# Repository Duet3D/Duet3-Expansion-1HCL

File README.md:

# Duet 3 Expansion 1HCL
The Duet 3 Expansion 1HCL is a CAN-FD connected expansion board for the [Duet 3 Mainboard 6HC](https://www.duet3d.com/duet3mainboard6hc), [Duet 3 Mainboard 6XD](https://www.duet3d.com/duet3mainboard6xd) and [Duet 3 Mini 5+](https://www.duet3d.com/duet3mini5plus) that is designed to provide a high current stepper motor driver, combined with multiple interfaces for position feedback. It has a number of peripheral inputs and outputs for functions such as sensing motor temperature, controlling a brake and axis endstop.

Product page is here: https://www.duet3d.com/duet-3-expansion-1hcl

Documentation is here: https://docs.duet3d.com/Duet3D_hardware/Duet_3_family/Duet_3_Expansion_1HCL

As always please discuss this on the Duet3d forum: https://forum.duet3d.com/

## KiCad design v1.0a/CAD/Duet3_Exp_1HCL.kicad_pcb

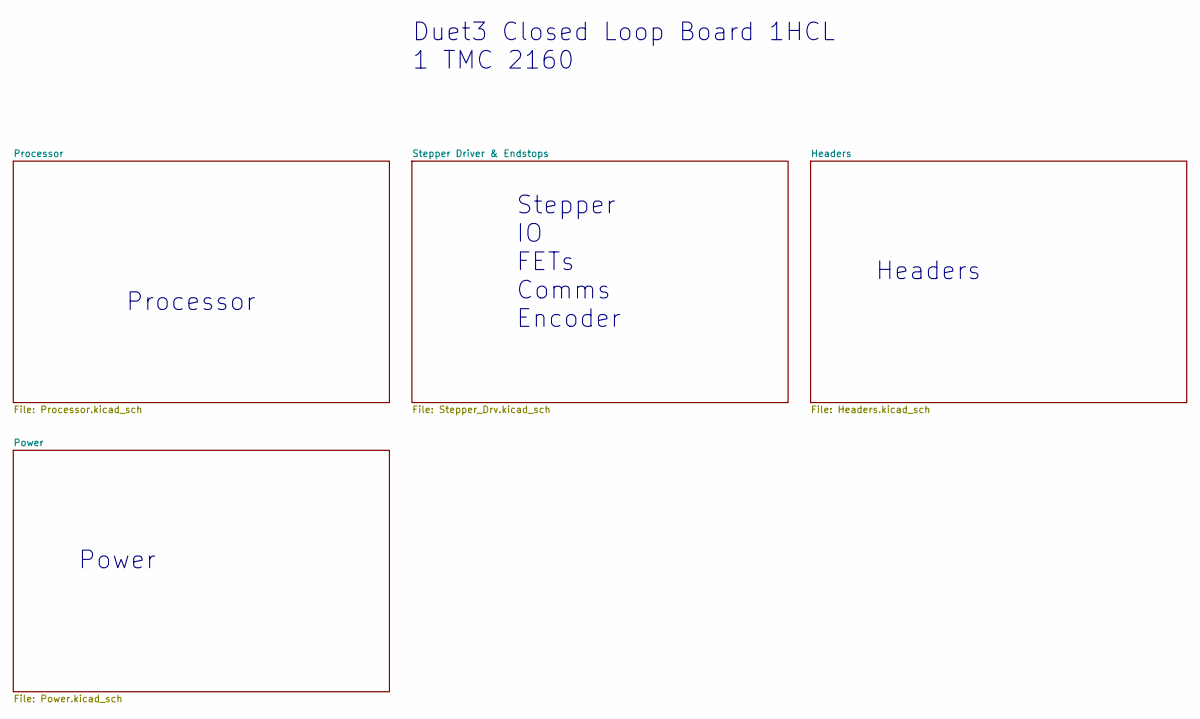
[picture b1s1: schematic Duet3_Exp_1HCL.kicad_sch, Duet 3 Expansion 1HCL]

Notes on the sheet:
Power
Duet3 Closed Loop Board 1HCL 1 TMC 2160
Processor
Stepper IO FETs Comms Encoder
Headers

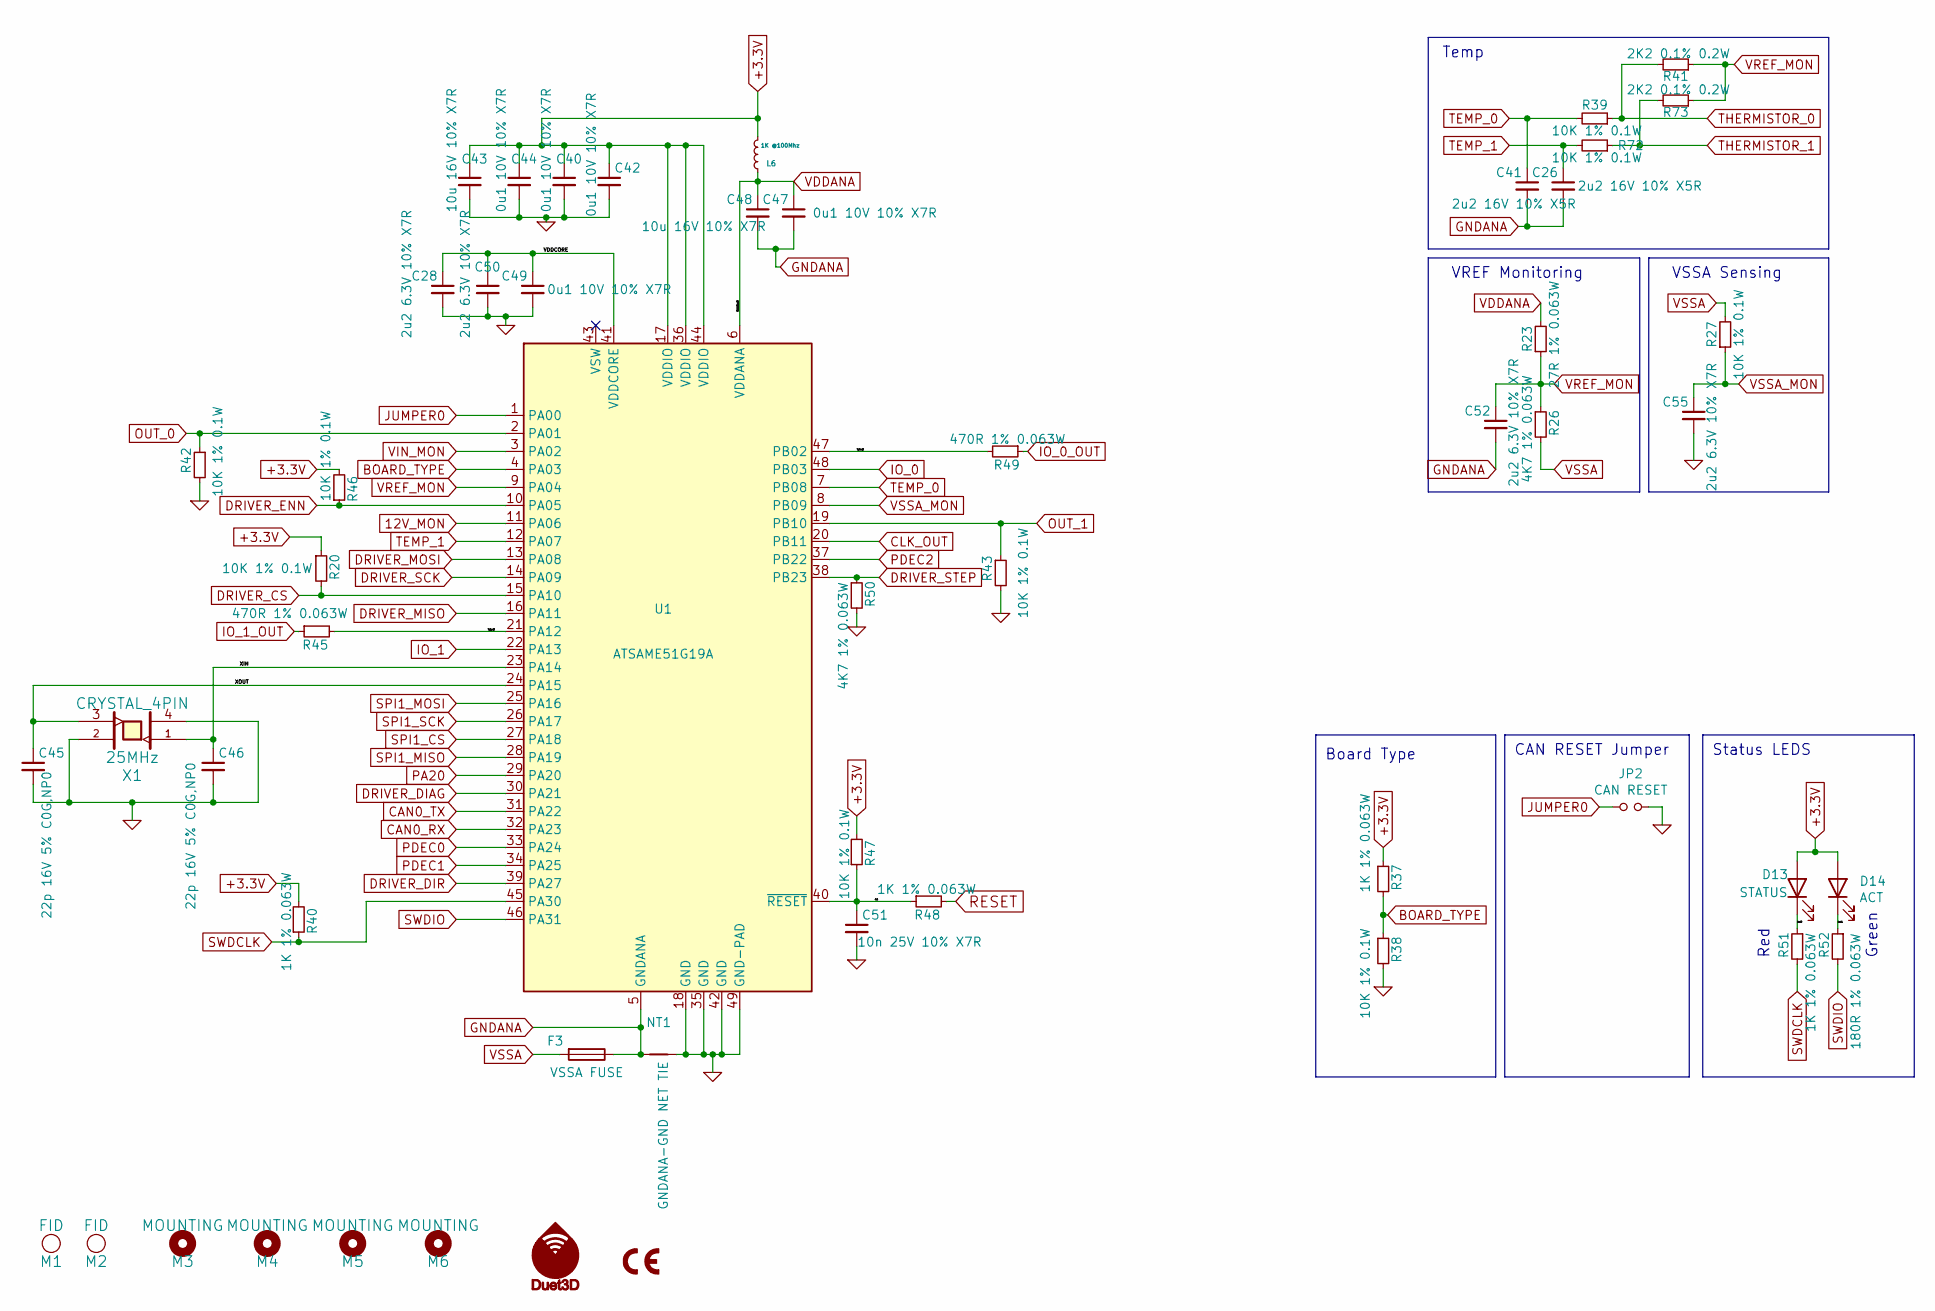
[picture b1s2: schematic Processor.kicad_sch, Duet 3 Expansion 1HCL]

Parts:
C26, C41: 2u2 16V 10% X5R; C_0603_1608Metric_Wbry; Part Number CL10A225KO8NNNC
C28, C50, C52, C55: 2u2 6.3V 10% X7R; C_0402_1005Metric_Wbry; Part Number CC0603KRX7R5BB225
C40, C42, C44, C47, C49: 0u1 10V 10% X7R; C_0402_1005Metric_Wbry; Part Number CL05B104KP5NNNC
C43, C48: 10u 16V 10% X7R; C_0805_2012Metric; Part Number CL21B106KOQNNNE
C45, C46: 22p 16V 5% C0G,NP0; C_0402_1005Metric_Wbry; Part Number C0402C220J4GACTU
C51: 10n 25V 10% X7R; C_0402_1005Metric_Wbry; Part Number CL05B103KA5VPNC
D13: STATUS; LED_0603_1608Metric; Part Number 150060RS75000 or equivalent Red
D14: ACT; LED_0603_1608Metric; Part Number 150060VS75000 or equivalent Green
F3: VSSA FUSE; Fuse_1206_3216Metric; Part Number 0ZCJ0020FF2E
JP2: CAN RESET; PinHeader_1x02_P2.54mm_Vertical; Part Number THS-02-R
L6: 1K @100Mhz; L_0603_1608Metric; Part Number 742792662 or PE-0603FB102ST or similar
M1, M2: FID; Fiducial_1mm_Mask2mm; Part Number virtual component - DNP
M3, M4, M5, M6: MOUNTING; MountingHole_3.2mm_M3; Part Number virtual component - DNP
M7: Duet3D_Logo; LOGO_NEW_Duet3D_vertical_6mm; Part Number virtual component - DNP
NT1: GNDANA-GND NET TIE; NetTie-2_SMD_Pad0.5mm; Part Number virtual component - DNP
R20, R27, R38, R39, R42, R43, R46, R47, R72: 10K 1% 0.1W; R_0402_1005Metric_Wbry; Part Number RK73H1ETTP1002F
R23: 27R 1% 0.063W; R_0402_1005Metric_Wbry; Part Number CRGCQ0402F27R
R26, R50: 4K7 1% 0.063W; R_0402_1005Metric_Wbry; Part Number RK73H1ETTP4701F
R37, R40, R48, R51: 1K 1% 0.063W; R_0402_1005Metric_Wbry; Part Number RMCF0402FT1K00
R41, R73: 2K2 0.1% 0.2W; R_0603_1608Metric_Wbry; Part Number RMCF0402FT2K20
R45, R49: 470R 1% 0.063W; R_0402_1005Metric_Wbry; Part Number RC0402FR-07470RL
R52: 180R 1% 0.063W; R_0402_1005Metric_Wbry; Part Number RMCF0402FT180R
U1: ATSAME51G19A; QFN-48-1EP_7x7mm_P0.5mm_EP5.2x5.2mm_ThermalVias; Part Number ATSAME51G19A
X1: CRYSTAL_4PIN; Crystal_SMD_ECS-33B-4Pin_3.2x2.5mm; Part Number TSX-3225 25.0000MF10P

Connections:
12V_MON: U1.11 (PA06); also elsewhere on the board
+3.3V: C40.1, C42.1, C43.1, C44.1, D13.2 (A), D14.2 (A), L6.1, R20.1, R37.1, R40.2, R46.2, R47.2, U1.17 (VDDIO), U1.36 (VDDIO), U1.44 (VDDIO); also elsewhere on the board
/Processor/VDDCORE: C28.1, C49.1, C50.1, U1.41 (VDDCORE)
/Processor/XIN: C46.1, U1.23 (PA14), X1.1
/Processor/XOUT: C45.1, U1.24 (PA15), X1.3
/Processor/io0out: R49.2, U1.47 (PB02)
/Processor/io1out: R45.2, U1.21 (PA12)
/Processor/led0: D13.1 (K), R51.1
/Processor/led1: D14.1 (K), R52.1
/Processor/rst: C51.1, R47.1, R48.1, U1.40 (~RESET)
BOARD_TYPE: R37.2, R38.1, U1.4 (PA03)
CAN0_RX: U1.32 (PA23); also elsewhere on the board
CAN0_TX: U1.31 (PA22); also elsewhere on the board
CLK_OUT: U1.20 (PB11); also elsewhere on the board
DRIVER_CS: R20.2, U1.15 (PA10); also elsewhere on the board
DRIVER_DIAG: U1.30 (PA21); also elsewhere on the board
DRIVER_DIR: U1.39 (PA27); also elsewhere on the board
DRIVER_ENN: R46.1, U1.10 (PA05); also elsewhere on the board
DRIVER_MISO: U1.16 (PA11); also elsewhere on the board
DRIVER_MOSI: U1.13 (PA08); also elsewhere on the board
DRIVER_SCK: U1.14 (PA09); also elsewhere on the board
DRIVER_STEP: R50.1, U1.38 (PB23); also elsewhere on the board
GND: C28.2, C40.2, C42.2, C43.2, C44.2, C45.2, C46.2, C49.2, C50.2, C51.2, C55.2, JP2.2, NT1.2, R38.2, R42.2, R43.2, R50.2, U1.18 (GND), U1.35 (GND), U1.42 (GND), U1.49 (GND-PAD), X1.2, X1.4; also elsewhere on the board
GNDANA: C26.2, C41.2, C47.2, C48.2, C52.2, F3.1, NT1.1, U1.5 (GNDANA)
IO_0: U1.48 (PB03); also elsewhere on the board
IO_0_OUT: R49.1; also elsewhere on the board
IO_1: U1.22 (PA13); also elsewhere on the board
IO_1_OUT: R45.1; also elsewhere on the board
JUMPER0: JP2.1, U1.1 (PA00)
OUT_0: R42.1, U1.2 (PA01); also elsewhere on the board
OUT_1: R43.1, U1.19 (PB10); also elsewhere on the board
PA20: U1.29 (PA20); also elsewhere on the board
PDEC0: U1.33 (PA24); also elsewhere on the board
PDEC1: U1.34 (PA25); also elsewhere on the board
PDEC2: U1.37 (PB22); also elsewhere on the board
RESET: R48.2; also elsewhere on the board
SPI1_CS: U1.27 (PA18); also elsewhere on the board
SPI1_MISO: U1.28 (PA19); also elsewhere on the board
SPI1_MOSI: U1.25 (PA16); also elsewhere on the board
SPI1_SCK: U1.26 (PA17); also elsewhere on the board
SWDCLK: R40.1, R51.2, U1.45 (PA30); also elsewhere on the board
SWDIO: R52.2, U1.46 (PA31); also elsewhere on the board
TEMP_0: C41.1, R39.2, U1.7 (PB08)
TEMP_1: C26.1, R72.2, U1.12 (PA07)
THERMISTOR_0: R39.1, R41.2; also elsewhere on the board
THERMISTOR_1: R72.1, R73.2; also elsewhere on the board
VDDANA: C47.1, C48.1, L6.2, R23.2, U1.6 (VDDANA)
VIN_MON: U1.3 (PA02); also elsewhere on the board
VREF_MON: C52.1, R23.1, R26.1, R41.1, R73.1, U1.9 (PA04)
VSSA: F3.2, R26.2, R27.2; also elsewhere on the board
VSSA_MON: C55.1, R27.1, U1.8 (PB09)

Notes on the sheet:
VREF Monitoring
Status LEDS
Red
Temp
Board Type
CAN RESET Jumper
Green
VSSA Sensing

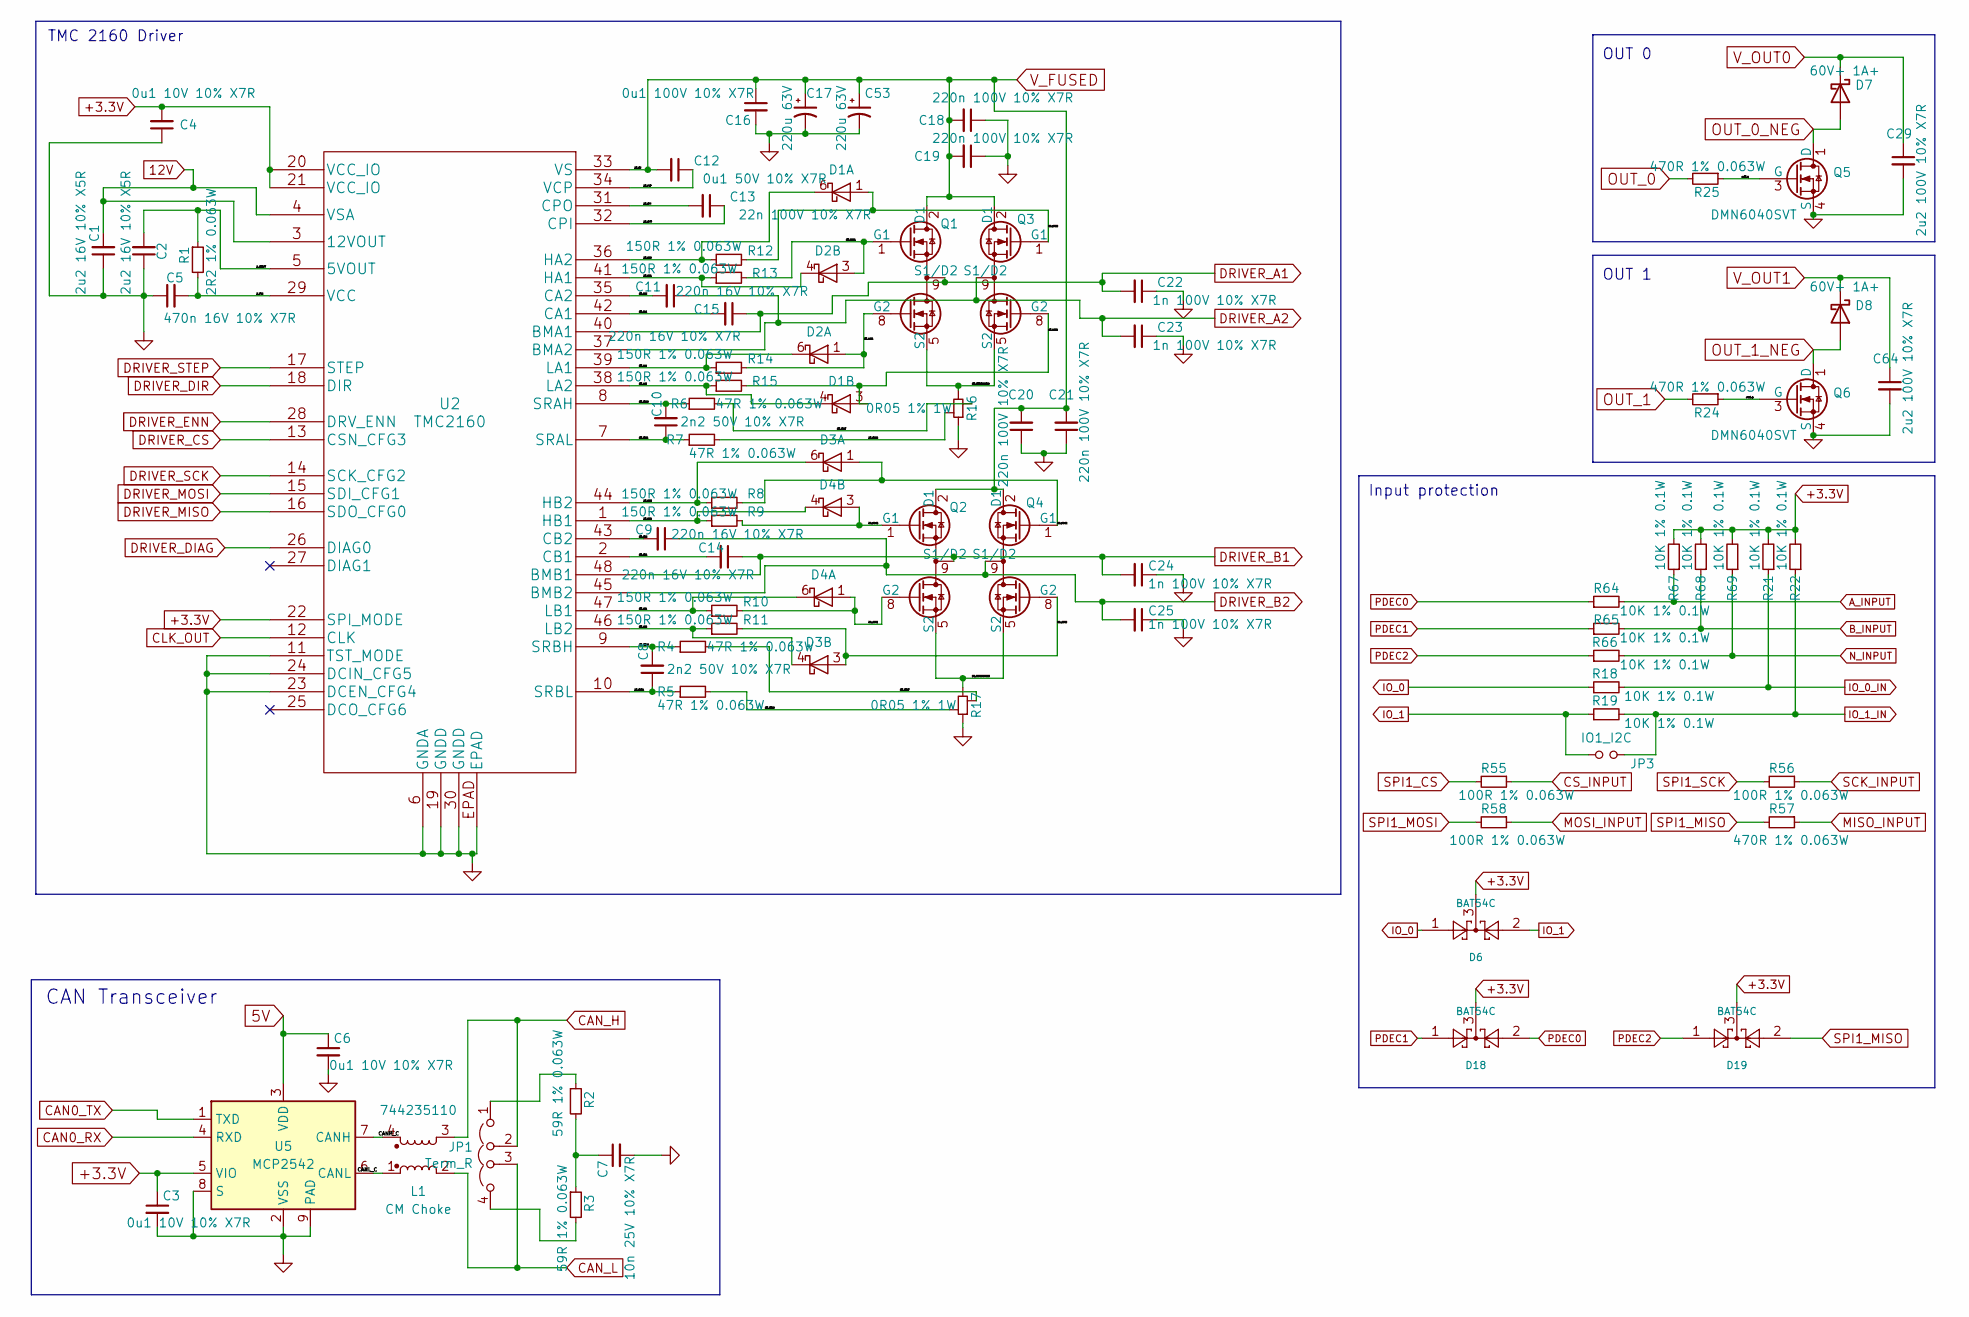
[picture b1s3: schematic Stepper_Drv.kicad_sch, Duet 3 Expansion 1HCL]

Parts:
C1, C2: 2u2 16V 10% X5R; C_0603_1608Metric_Wbry; Part Number CL10A225KO8NNNC
C3, C4, C6: 0u1 10V 10% X7R; C_0402_1005Metric_Wbry; Part Number CL05B104KP5NNNC
C5: 470n 16V 10% X7R; C_0603_1608Metric_Wbry; Part Number CL10B474KO8NNNC
C7: 10n 25V 10% X7R; C_0402_1005Metric_Wbry; Part Number CL05B103KA5VPNC
C8, C10: 2n2 50V 10% X7R; C_0402_1005Metric_Wbry; Part Number GCM155R71H222KA37D
C9, C11, C14, C15: 220n 16V 10% X7R; C_0603_1608Metric_Wbry; Part Number CL10B224KO8NNNC
C12: 0u1 50V 10% X7R; C_0603_1608Metric_Wbry; Part Number CL10B104KB8NNNC
C13: 22n 100V 10% X7R; C_0603_1608Metric_Wbry; Part Number C0603C223K1RACTU
C16: 0u1 100V 10% X7R; C_0603_1608Metric_Wbry; Part Number HMK107B7104MA-T or similar
C17, C53: 220u 63V; CP_Elec_12.5x14; Part Number 865060762009
C18, C19, C20, C21: 220n 100V 10% X7R; C_1206_3216Metric; Part Number C3216X7R2A224K115AA
C22, C23, C24, C25: 1n 100V 10% X7R; C_0603_1608Metric_Wbry; Part Number CGA3E2X7R2A102K080AA
C29, C64: 2u2 100V 10% X7R; C_1210_3225Metric; Part Number CL32B225KCJSNNE
D1, D2, D3, D4: BAT40V; SOT-563; Part Number BAT40V-7
D6, D18, D19: BAT54C; SOT-23; Part Number BAT54CLT1G
D7, D8: 60V+ 1A+; D_SMF; Part Number SS1FH10-M3/H or equivalent
JP1: Term_R; PinHeader_1x04_P2.54mm_Vertical; Part Number THS-04-R
JP3: IO1_I2C; PinHeader_1x02_P2.54mm_Vertical; Part Number THS-02-R
L1: CM Choke; Wurth_CM_Choke_1812_744235nnn; Part Number 744235110
Q1, Q2, Q3, Q4: SIZ250DT; Vishay_PowerPAIR3x3S; Part Number SIZ250DT-T1-GE3
Q5, Q6: DMN6040SVT; SOT-23-6-DMN6040SVT; Part Number DMN6040SVT
R1: 2R2 1% 0.063W; R_0402_1005Metric_Wbry; Part Number RMCF0402FT2R20
R2, R3: 59R 1% 0.063W; R_0402_1005Metric_Wbry; Part Number RMCF0402FT59R0
R4, R5, R6, R7: 47R 1% 0.063W; R_0603_1608Metric_Wbry; Part Number RMCF0402FT47R0
R8, R9, R10, R11, R12, R13, R14, R15: 150R 1% 0.063W; R_0402_1005Metric_Wbry; Part Number RMCF0402FT150R
R16, R17: 0R05 1% 1W; R_1206_SenseResistorKelvin; Part Number PE1206FRE470R05L or ERJ-8CWFR050V or si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
R18, R19, R21, R22, R64, R65, R66, R67, R68, R69: 10K 1% 0.1W; R_0402_1005Metric_Wbry; Part Number RK73H1ETTP1002F
R24, R25, R57: 470R 1% 0.063W; R_0402_1005Metric_Wbry; Part Number RC0402FR-07470RL
R55, R56, R58: 100R 1% 0.063W; R_0402_1005Metric_Wbry; Part Number CRGCQ0402F100R
U2: TMC2160; TMC5160-TA; Part Number TMC2160A-TA
U5: MCP2542; DFN-8-1EP_3x2mm_P0.5mm_EP1.3x1.5mm; Part Number MCP2542FDT-E/MNY

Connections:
5V: C6.1, U5.3 (VDD); also elsewhere on the board
12V: C1.2, U2.3 (12VOUT), U2.4 (VSA); also elsewhere on the board
+3.3V: C3.1, C4.2, D6.3, D18.3, D19.3, R21.2, R22.2, R67.2, R68.2, R69.2, U2.20 (VCC_IO), U2.21 (VCC_IO), U2.22 (SPI_MODE), U5.5 (VIO); also elsewhere on the board
/Stepper Driver & Endstops/CANH_C: L1.4, U5.7 (CANH)
/Stepper Driver & Endstops/CANL_C: L1.1, U5.6 (CANL)
/Stepper Driver & Endstops/D0_CA1: C15.2, U2.42 (CA1)
/Stepper Driver & Endstops/D0_CA2: C11.2, U2.35 (CA2)
/Stepper Driver & Endstops/D0_CB1: C14.2, U2.2 (CB1)
/Stepper Driver & Endstops/D0_CB2: C9.2, U2.43 (CB2)
/Stepper Driver & Endstops/D0_CPI: C13.2, U2.31 (CPO)
/Stepper Driver & Endstops/D0_CPO: C13.1, U2.32 (CPI)
/Stepper Driver & Endstops/D0_FETSOURCEA: Q1.5 (S2), Q1.6 (S2), Q1.7 (S2), Q3.5 (S2), Q3.6 (S2), Q3.7 (S2), R16.2
/Stepper Driver & Endstops/D0_FETSOURCEB: Q2.5 (S2), Q2.6 (S2), Q2.7 (S2), Q4.5 (S2), Q4.6 (S2), Q4.7 (S2), R17.2
/Stepper Driver & Endstops/D0_HA1: D2.4 (C), R13.1, U2.41 (HA1)
/Stepper Driver & Endstops/D0_HA2: D1.6 (C), R12.1, U2.36 (HA2)
/Stepper Driver & Endstops/D0_HAG1: D2.3 (A), Q1.1 (G1), R13.2
/Stepper Driver & Endstops/D0_HAG2: D1.1 (A), Q3.1 (G1), R12.2
/Stepper Driver & Endstops/D0_HB1: D4.4 (C), R9.1, U2.1 (HB1)
/Stepper Driver & Endstops/D0_HB2: D3.6 (C), R8.1, U2.44 (HB2)
/Stepper Driver & Endstops/D0_HBG1: D4.3 (A), Q2.1 (G1), R9.2
/Stepper Driver & Endstops/D0_HBG2: D3.1 (A), Q4.1 (G1), R8.2
/Stepper Driver & Endstops/D0_LA1: D2.6 (C), R14.1, U2.39 (LA1)
/Stepper Driver & Endstops/D0_LA2: D1.4 (C), R15.1, U2.38 (LA2)
/Stepper Driver & Endstops/D0_LAG1: D2.1 (A), Q1.8 (G2), R14.2
/Stepper Driver & Endstops/D0_LAG2: D1.3 (A), Q3.8 (G2), R15.2
/Stepper Driver & Endstops/D0_LB1: D4.6 (C), R10.1, U2.47 (LB1)
/Stepper Driver & Endstops/D0_LB2: D3.4 (C), R11.1, U2.46 (LB2)
/Stepper Driver & Endstops/D0_LBG1: D4.1 (A), Q2.8 (G2), R10.2
/Stepper Driver & Endstops/D0_LBG2: D3.3 (A), Q4.8 (G2), R11.2
/Stepper Driver & Endstops/D0_SRAG: R7.2, R16.3
/Stepper Driver & Endstops/D0_SRAH: C10.2, R6.1, U2.8 (SRAH)
/Stepper Driver & Endstops/D0_SRAL: C10.1, R7.1, U2.7 (SRAL)
/Stepper Driver & Endstops/D0_SRAT: R6.2, R16.4
/Stepper Driver & Endstops/D0_SRBG: R5.2, R17.3
/Stepper Driver & Endstops/D0_SRBH: C8.2, R4.1, U2.9 (SRBH)
/Stepper Driver & Endstops/D0_SRBL: C8.1, R5.1, U2.10 (SRBL)
/Stepper Driver & Endstops/D0_SRBT: R4.2, R17.4
/Stepper Driver & Endstops/D0_VCP: C12.1, U2.34 (VCP)
/Stepper Driver & Endstops/D_5VOUT: C2.2, R1.1, U2.5 (5VOUT)
/Stepper Driver & Endstops/D_VCC: C5.2, R1.2, U2.29 (VCC)
/Stepper Driver & Endstops/out0_g: Q5.3 (G), R25.1
/Stepper Driver & Endstops/out1_g: Q6.3 (G), R24.1
A_INPUT: R64.2, R67.1; also elsewhere on the board
B_INPUT: R65.2, R68.1; also elsewhere on the board
CAN0_RX: U5.4 (RXD); also elsewhere on the board
CAN0_TX: U5.1 (TXD); also elsewhere on the board
CAN_H: JP1.2 (C), L1.3; also elsewhere on the board
CAN_L: JP1.3 (C), L1.2; also elsewhere on the board
CLK_OUT: U2.12 (CLK); also elsewhere on the board
CS_INPUT: R55.1; also elsewhere on the board
DRIVER_A1: C15.1, C22.2, Q1.9 (S1/D2), U2.40 (BMA1); also elsewhere on the board
DRIVER_A2: C11.1, C23.2, Q3.9 (S1/D2), U2.37 (BMA2); also elsewhere on the board
DRIVER_B1: C14.1, C24.2, Q2.9 (S1/D2), U2.48 (BMB1); also elsewhere on the board
DRIVER_B2: C9.1, C25.2, Q4.9 (S1/D2), U2.45 (BMB2); also elsewhere on the board
DRIVER_CS: U2.13 (CSN_CFG3); also elsewhere on the board
DRIVER_DIAG: U2.26 (DIAG0); also elsewhere on the board
DRIVER_DIR: U2.18 (DIR); also elsewhere on the board
DRIVER_ENN: U2.28 (DRV_ENN); also elsewhere on the board
DRIVER_MISO: U2.16 (SDO_CFG0); also elsewhere on the board
DRIVER_MOSI: U2.15 (SDI_CFG1); also elsewhere on the board
DRIVER_SCK: U2.14 (SCK_CFG2); also elsewhere on the board
DRIVER_STEP: U2.17 (STEP); also elsewhere on the board
GND: C1.1, C2.1, C3.2, C4.1, C5.1, C6.2, C7.2, C16.2, C17.2, C18.1, C19.1, C20.1, C21.1, C22.1, C23.1, C24.1, C25.1, C29.2, C53.2, C64.2, Q5.4 (S), Q6.4 (S), R16.1, R17.1, U2.6 (GNDA), U2.11 (TST_MODE), U2.19 (GNDD), U2.23 (DCEN_CFG4), U2.24 (DCIN_CFG5), U2.30 (GNDD), U2.EPAD, U5.2 (VSS), U5.8 (S), U5.9 (PAD); also elsewhere on the board
IO_0: D6.1, R18.1; also elsewhere on the board
IO_0_IN: R18.2, R21.1; also elsewhere on the board
IO_1: D6.2, JP3.1, R19.1; also elsewhere on the board
IO_1_IN: JP3.2, R19.2, R22.1; also elsewhere on the board
MISO_INPUT: R57.1; also elsewhere on the board
MOSI_INPUT: R58.1; also elsewhere on the board
N_INPUT: R66.2, R69.1; also elsewhere on the board
unnamed: C7.1, R2.2, R3.1
unnamed: JP1.1 (A), R2.1
unnamed: JP1.4 (B), R3.2
OUT_0: R25.2; also elsewhere on the board
OUT_0_NEG: D7.2 (A), Q5.1 (D), Q5.2 (D), Q5.5 (D), Q5.6 (D); also elsewhere on the board
OUT_1: R24.2; also elsewhere on the board
OUT_1_NEG: D8.2 (A), Q6.1 (D), Q6.2 (D), Q6.5 (D), Q6.6 (D); also elsewhere on the board
PDEC0: D18.2, R64.1; also elsewhere on the board
PDEC1: D18.1, R65.1; also elsewhere on the board
PDEC2: D19.1, R66.1; also elsewhere on the board
SCK_INPUT: R56.1; also elsewhere on the board
SPI1_CS: R55.2; also elsewhere on the board
SPI1_MISO: D19.2, R57.2; also elsewhere on the board
SPI1_MOSI: R58.2; also elsewhere on the board
SPI1_SCK: R56.2; also elsewhere on the board
V_FUSED: C12.2, C16.1, C17.1, C18.2, C19.2, C20.2, C21.2, C53.1, Q1.2 (D1), Q1.3 (D1), Q1.4 (D1), Q1.10 (D1), Q2.2 (D1), Q2.3 (D1), Q2.4 (D1), Q2.10 (D1), Q3.2 (D1), Q3.3 (D1), Q3.4 (D1), Q3.10 (D1), Q4.2 (D1), Q4.3 (D1), Q4.4 (D1), Q4.10 (D1), U2.33 (VS); also elsewhere on the board
V_OUT0: C29.1, D7.1 (K); also elsewhere on the board
V_OUT1: C64.1, D8.1 (K); also elsewhere on the board

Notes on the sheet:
Input protection
OUT 0
CAN Transceiver
TMC 2160 Driver
OUT 1

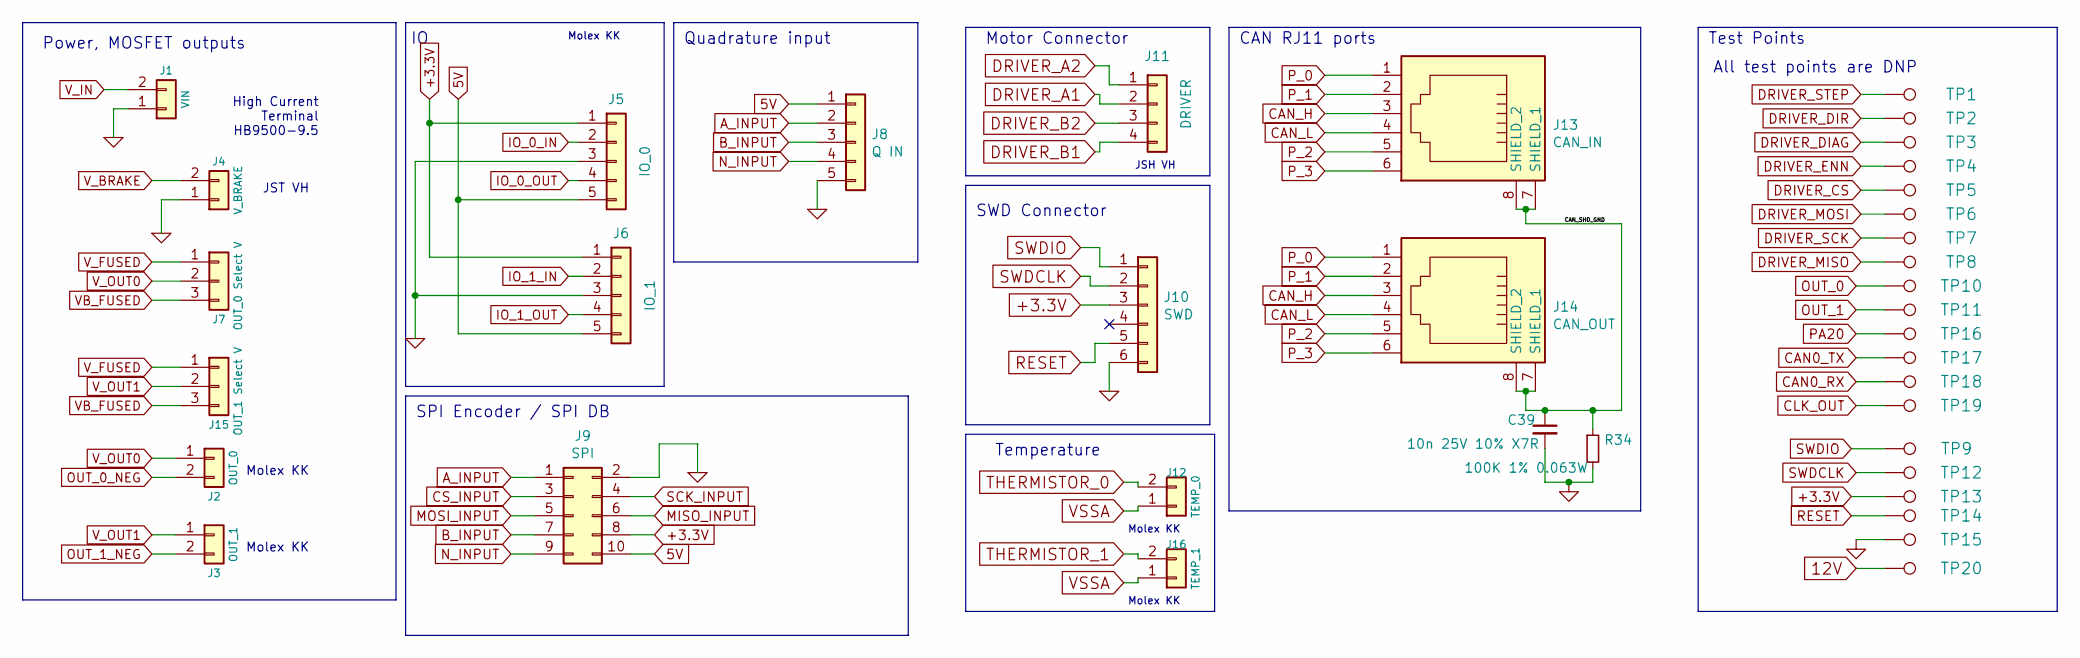
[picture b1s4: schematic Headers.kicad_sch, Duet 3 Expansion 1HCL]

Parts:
C39: 10n 25V 10% X7R; C_0402_1005Metric_Wbry; Part Number CL05B103KA5VPNC
J1: VIN; screwt-barrier-9.5mm-1x2; Part Number HB950-9.50-2P
J2: OUT_0; Wurth_61900211121-1x02_P2.54mm_Vertical-(Molex_KK-254_AE-64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; Part Number 61900211121
J3: OUT_1; Wurth_61900211121-1x02_P2.54mm_Vertical-(Molex_KK-254_AE-64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; Part Number 61900211121
J4: V_BRAKE; JST_VH_B2P-VH_1x02_P3.96mm_Vertical; Part Number B2P-VH(LF)(SN)
J5: IO_0; Wurth_61900511121-1x05_P2.54mm_Vertical(Molex_KK-254_AE-641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; Part Number 61900511121
J6: IO_1; Wurth_61900511121-1x05_P2.54mm_Vertical(Molex_KK-254_AE-641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; Part Number 61900511121
J7: OUT_0 Select V; PinHeader_1x03_P2.54mm_Vertical; Part Number THS-03-R
J8: Q IN; Wurth_61900511121-1x05_P2.54mm_Vertical(Molex_KK-254_AE-641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; Part Number 61900511121
J9: SPI; IDC-Header_2x05_P2.54mm_Vertical; Part Number 61201021621
J10: SWD; JST_ZH_1x06_P1.5_B6B-ZR-SM4-TF; Part Number B6B-ZR(LF)(SN)
J11: DRIVER; JST_VH_B4P-VH_1x04_P3.96mm_Vertical; Part Number B4P-VH(LF)(SN)
J12: TEMP_0; Wurth_61900211121-1x02_P2.54mm_Vertical-(Molex_KK-254_AE-64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; Part Number 61900211121
J13: CAN_IN; RJ11_6P6C_half_shield; Part Number Wurth 615 006 143 421 or equivalent
J14: CAN_OUT; RJ11_6P6C_half_shield; Part Number Wurth 615 006 143 421 or equivalent
J15: OUT_1 Select V; PinHeader_1x03_P2.54mm_Vertical; Part Number THS-03-R
J16: TEMP_1; Wurth_61900211121-1x02_P2.54mm_Vertical-(Molex_KK-254_AE-64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; Part Number 61900211121
R34: 100K 1% 0.063W; R_0402_1005Metric_Wbry; Part Number RMCF0402FT100K
TP1: STEP; TestPoint_Pad_D2.0mm; Part Number virtual component - DNP
TP2: DIR; TestPoint_Pad_D2.0mm; Part Number virtual component - DNP
TP3: DIAG; TestPoint_Pad_D2.0mm; Part Number virtual component - DNP
TP4: ENN; TestPoint_Pad_D2.0mm; Part Number virtual component - DNP
TP5: D_CS; TestPoint_Pad_D2.0mm; Part Number virtual component - DNP
TP6: D_MOSI; TestPoint_Pad_D2.0mm; Part Number virtual component - DNP
TP7: D_SCK; TestPoint_Pad_D2.0mm; Part Number virtual component - DNP
TP8: D_MISO; TestPoint_Pad_D2.0mm; Part Number virtual component - DNP
TP9: SWDIO; TestPoint_Pad_D2.0mm; Part Number virtual component - DNP
TP10: OUT_0; TestPoint_Pad_D2.0mm; Part Number virtual component - DNP
TP11: OUT_1; TestPoint_Pad_D2.0mm; Part Number virtual component - DNP
TP12: SWDCLK; TestPoint_Pad_D2.0mm; Part Number virtual component - DNP
TP13: +3.3V; TestPoint_Pad_D2.0mm; Part Number virtual component - DNP
TP14: RST; TestPoint_Pad_D2.0mm; Part Number virtual component - DNP
TP15: GND; TestPoint_Pad_D2.0mm; Part Number virtual component - DNP
TP16: PA20; TestPoint_Pad_D2.0mm; Part Number virtual component - DNP
TP17: CAN0_TX; TestPoint_Pad_D2.0mm; Part Number virtual component - DNP
TP18: CAN0_RX; TestPoint_Pad_D2.0mm; Part Number virtual component - DNP
TP19: CLK_OUT; TestPoint_Pad_D2.0mm; Part Number virtual component - DNP
TP20: 12V; TestPoint_Pad_D2.0mm; Part Number virtual component - DNP

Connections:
5V: J5.5, J6.5, J8.1, J9.10; also elsewhere on the board
12V: TP20.1; also elsewhere on the board
+3.3V: J5.1, J6.1, J9.8, J10.3, TP13.1; also elsewhere on the board
/Headers/CAN_SHD_GND: C39.1, J13.7 (SHIELD_1), J13.8 (SHIELD_2), J14.7 (SHIELD_1), J14.8 (SHIELD_2), R34.1
A_INPUT: J8.2, J9.1; also elsewhere on the board
B_INPUT: J8.3, J9.7; also elsewhere on the board
CAN0_RX: TP18.1; also elsewhere on the board
CAN0_TX: TP17.1; also elsewhere on the board
CAN_H: J13.3, J14.3; also elsewhere on the board
CAN_L: J13.4, J14.4; also elsewhere on the board
CLK_OUT: TP19.1; also elsewhere on the board
CS_INPUT: J9.3; also elsewhere on the board
DRIVER_A1: J11.2; also elsewhere on the board
DRIVER_A2: J11.1; also elsewhere on the board
DRIVER_B1: J11.4; also elsewhere on the board
DRIVER_B2: J11.3; also elsewhere on the board
DRIVER_CS: TP5.1; also elsewhere on the board
DRIVER_DIAG: TP3.1; also elsewhere on the board
DRIVER_DIR: TP2.1; also elsewhere on the board
DRIVER_ENN: TP4.1; also elsewhere on the board
DRIVER_MISO: TP8.1; also elsewhere on the board
DRIVER_MOSI: TP6.1; also elsewhere on the board
DRIVER_SCK: TP7.1; also elsewhere on the board
DRIVER_STEP: TP1.1; also elsewhere on the board
GND: C39.2, J1.1, J4.1, J5.3, J6.3, J8.5, J9.2, J10.6, R34.2, TP15.1; also elsewhere on the board
IO_0_IN: J5.2; also elsewhere on the board
IO_0_OUT: J5.4; also elsewhere on the board
IO_1_IN: J6.2; also elsewhere on the board
IO_1_OUT: J6.4; also elsewhere on the board
MISO_INPUT: J9.6; also elsewhere on the board
MOSI_INPUT: J9.5; also elsewhere on the board
N_INPUT: J8.4, J9.9; also elsewhere on the board
OUT_0: TP10.1; also elsewhere on the board
OUT_0_NEG: J2.2; also elsewhere on the board
OUT_1: TP11.1; also elsewhere on the board
OUT_1_NEG: J3.2; also elsewhere on the board
PA20: TP16.1; also elsewhere on the board
P_0: J13.1, J14.1
P_1: J13.2, J14.2
P_2: J13.5, J14.5
P_3: J13.6, J14.6
RESET: J10.5, TP14.1; also elsewhere on the board
SCK_INPUT: J9.4; also elsewhere on the board
SWDCLK: J10.2, TP12.1; also elsewhere on the board
SWDIO: J10.1, TP9.1; also elsewhere on the board
THERMISTOR_0: J12.2; also elsewhere on the board
THERMISTOR_1: J16.2; also elsewhere on the board
VB_FUSED: J7.3, J15.3; also elsewhere on the board
VSSA: J12.1, J16.1; also elsewhere on the board
V_BRAKE: J4.2; also elsewhere on the board
V_FUSED: J7.1, J15.1; also elsewhere on the board
V_IN: J1.2; also elsewhere on the board
V_OUT0: J2.1, J7.2; also elsewhere on the board
V_OUT1: J3.1, J15.2; also elsewhere on the board

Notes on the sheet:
Motor Connector
JSH VH
All test points are DNP
Power, MOSFET outputs
High Current Terminal HB9500-9.5
JST VH
Molex KK
Test Points
SPI Encoder / SPI DB
Quadrature input
CAN RJ11 ports
Temperature
SWD Connector
